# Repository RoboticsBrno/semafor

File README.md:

# Semafor

Traffic light gadget for outdoor games designed for [Helceletka.cz](https://helceletka.cz/).

## Hardware
Board is based on [ESP8266](https://en.wikipedia.org/wiki/ESP8266) microcontroller and large LEDs. It is powered by our power bank and can be managed via WiFi from the user's phone.

## Software
The software is written in [PlatformIO](https://platformio.org/) and is based on the Arduino framework.

<div align="center">
  	<td></td>
	<td></td>
</div>

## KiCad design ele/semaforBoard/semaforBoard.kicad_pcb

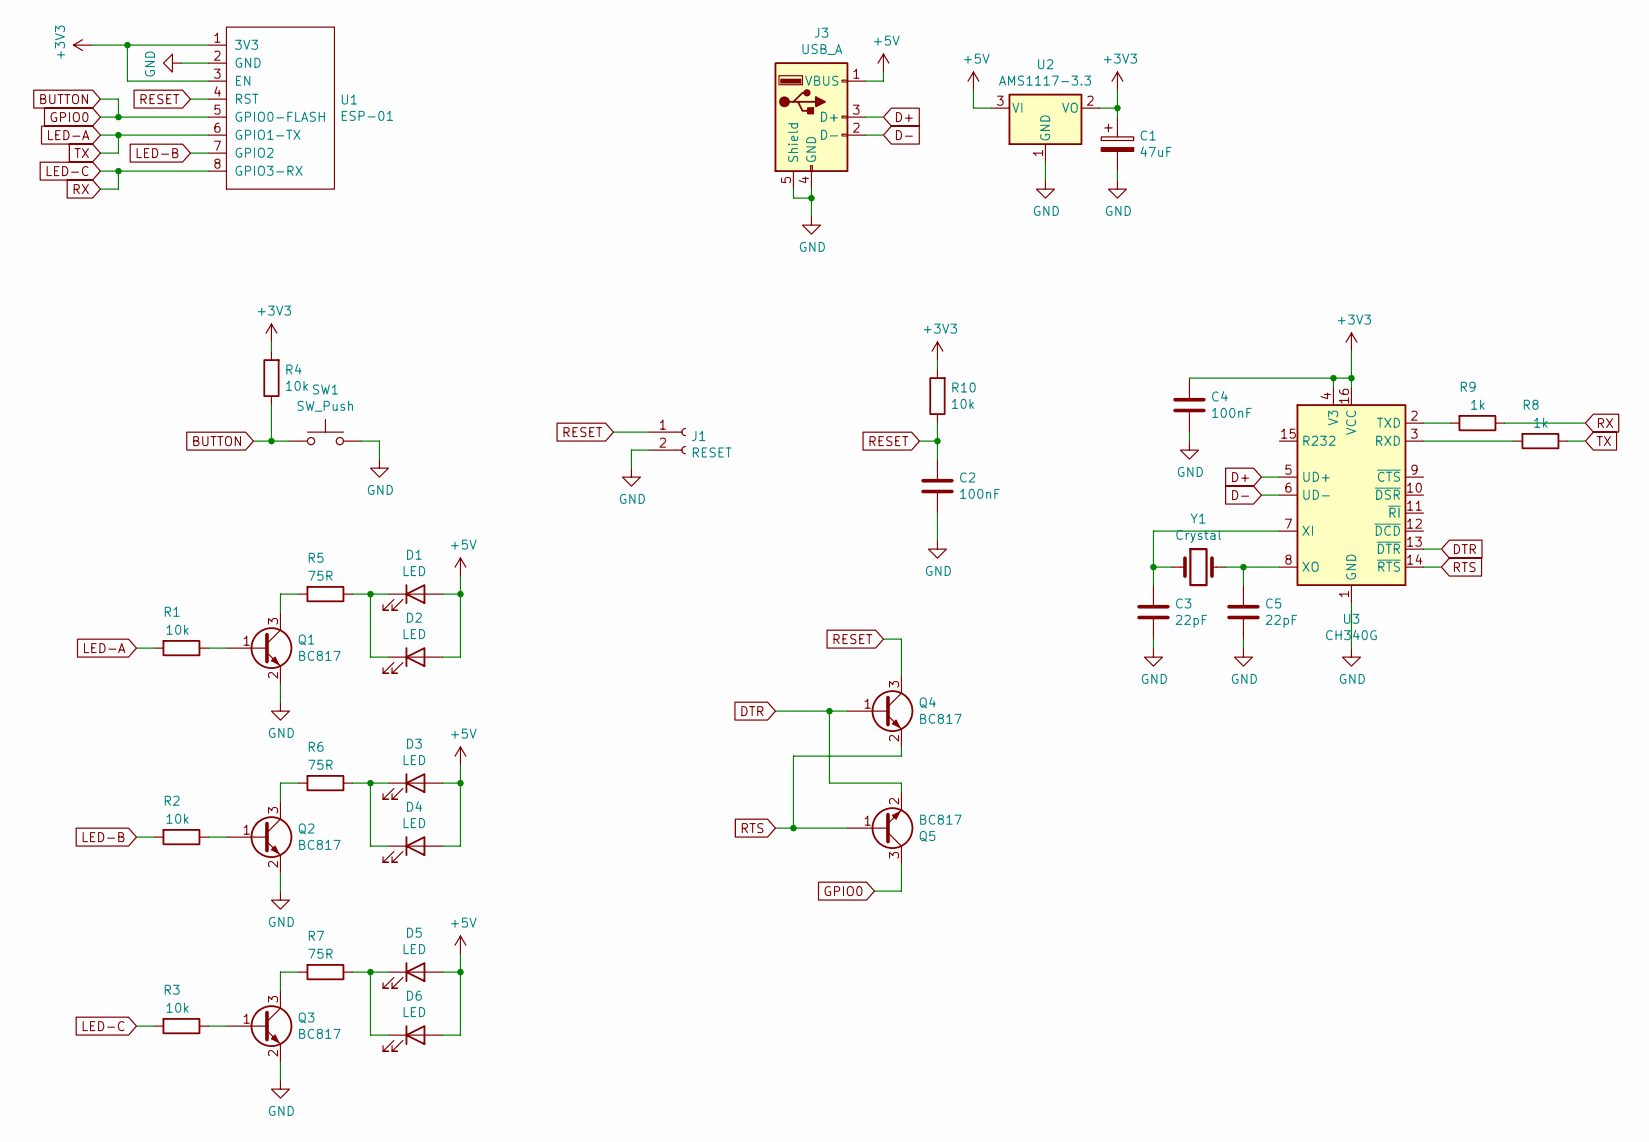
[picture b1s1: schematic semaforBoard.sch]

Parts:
C1: 47uF; CP_Radial_D6.3mm_P2.50mm
C2, C4: 100nF; C_1206_3216Metric_Pad1.42x1.75mm_HandSolder
C3, C5: 22pF; C_1206_3216Metric_Pad1.42x1.75mm_HandSolder
D1, D2, D3, D4, D5, D6: LED; LED_D10.0mm
J1: RESET; PinHeader_1x02_P2.54mm_Vertical
J3: USB_A; USB_A_CNCTech_1001-011-01101_Horizontal
Q1, Q2, Q3, Q4, Q5: BC817; SOT-23
R1, R2, R3, R4, R10: 10k; R_1206_3216Metric_Pad1.42x1.75mm_HandSolder
R5, R6, R7: 75R; R_1206_3216Metric_Pad1.42x1.75mm_HandSolder
R8, R9: 1k; R_1206_3216Metric_Pad1.42x1.75mm_HandSolder
SW1: SW_Push; SW_PUSH_6mm
U1: ESP-01
U2: AMS1117-3.3; SOT-223-3_TabPin2
U3: CH340G; SOIC-16_3.9x9.9mm_P1.27mm
Y1: Crystal; Crystal_HC49-4H_Vertical

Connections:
+3V3: C1.1, C4.1, R4.2, R10.2, U1.1 (3V3), U1.3 (EN), U2.2 (VO), U3.4 (V3), U3.16 (VCC)
+5V: D1.2 (A), D2.2 (A), D3.2 (A), D4.2 (A), D5.2 (A), D6.2 (A), J3.1 (VBUS), U2.3 (VI)
BUTTON: Q5.3 (C), R4.1, SW1.1, U1.5 (GPIO0-FLASH)
D+: J3.3 (D+), U3.5 (UD+)
D-: J3.2 (D-), U3.6 (UD-)
DTR: Q4.1 (B), Q5.2 (E), U3.13 (~DTR)
GND: C1.2, C2.2, C3.2, C4.2, C5.2, J1.2, J3.4 (GND), J3.5 (Shield), Q1.2 (E), Q2.2 (E), Q3.2 (E), SW1.2, U1.2 (GND), U2.1 (GND), U3.1 (GND)
LED-A: R1.2, R8.1, U1.6 (GPIO1-TX)
LED-B: R2.2, U1.7 (GPIO2)
LED-C: R3.2, R9.1, U1.8 (GPIO3-RX)
unnamed: C3.1, U3.7 (XI), Y1.1
unnamed: C5.1, U3.8 (XO), Y1.2
unnamed: D1.1 (K), D2.1 (K), R5.1
unnamed: D3.1 (K), D4.1 (K), R6.1
unnamed: D5.1 (K), D6.1 (K), R7.1
unnamed: Q1.1 (B), R1.1
unnamed: Q1.3 (C), R5.2
unnamed: Q2.1 (B), R2.1
unnamed: Q2.3 (C), R6.2
unnamed: Q3.1 (B), R3.1
unnamed: Q3.3 (C), R7.2
unnamed: R8.2, U3.3 (RXD)
unnamed: R9.2, U3.2 (TXD)
RESET: C2.1, J1.1, Q4.3 (C), R10.1, U1.4 (RST)
RTS: Q4.2 (E), Q5.1 (B), U3.14 (~RTS)

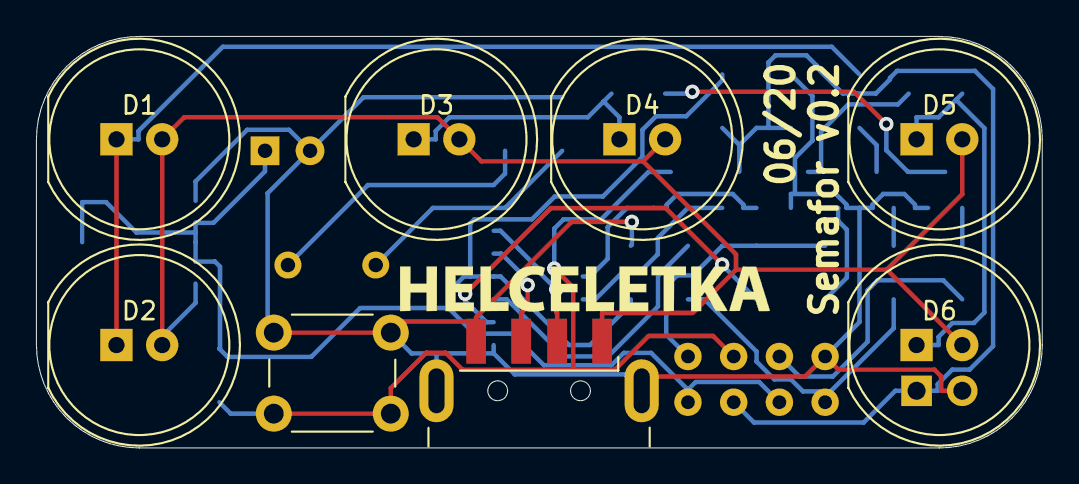
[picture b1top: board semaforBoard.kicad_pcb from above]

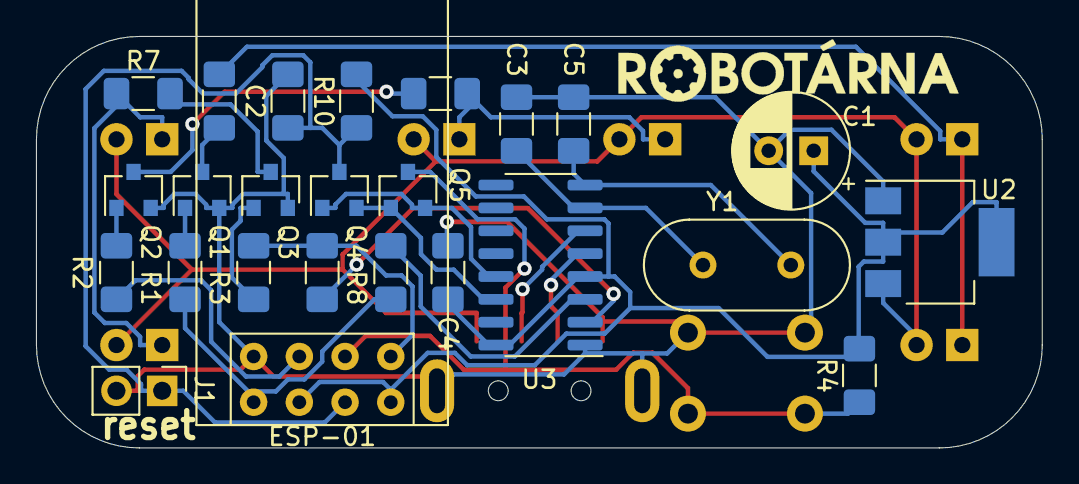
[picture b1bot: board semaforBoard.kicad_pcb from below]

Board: 2 copper layers, 55.9 x 22.9 mm, 35 parts (26 on the bottom side), 25 nets.

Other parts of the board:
G1: LOGO; Robotarna
G2: LOGO; Helceletka

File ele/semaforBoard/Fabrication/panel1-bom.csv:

"Id";"Designator";"Package";"Quantity";"Designation";"Supplier and ref";
1;"REF**,REF**,REF**,REF**,REF**,REF**,REF**,REF**,REF**,REF**,REF**,REF**,REF**,REF**,REF**,REF**,REF**,REF**,REF**,REF**,REF**,REF**,REF**,REF**,REF**,REF**,REF**,REF**,REF**,REF**,REF**,REF**,REF**,REF**,REF**,REF**,REF**,REF**,REF**,REF**,REF**,REF**,REF**,REF**,REF**,REF**,REF**,REF**,REF**,REF**,REF**,REF**,REF**,REF**,REF**,REF**,REF**,REF**,REF**,REF**,REF**,REF**,REF**,REF**,REF**,REF**,REF**,REF**,REF**,REF**,REF**,REF**,REF**,REF**,REF**,REF**,REF**,REF**,REF**,REF**,REF**,REF**,REF**,REF**,REF**,REF**,REF**,REF**,REF**,REF**,REF**,REF**,REF**,REF**,REF**,REF**,REF**,REF**,REF**,REF**,REF**,REF**,REF**,REF**,REF**,REF**,REF**,REF**";"NPTH";108;"NPTH";;;
2;"J1,J1,J1,J1";"PinHeader_1x02_P2.54mm_Vertical";4;"RESET";;;
3;"D6,D5,D4,D3,D2,D1,D6,D5,D4,D3,D2,D1,D6,D5,D4,D3,D2,D1,D6,D5,D4,D3,D2,D1";"LED_D10.0mm";24;"LED";;;
4;"Y1,Y1,Y1,Y1";"Crystal_HC49-4H_Vertical";4;"Crystal";;;
5;"U3,U3,U3,U3";"SOIC-16_3.9x9.9mm_P1.27mm";4;"CH340G";;;
6;"R10,R4,R3,R2,R1,R10,R4,R3,R2,R1,R10,R4,R3,R2,R1,R10,R4,R3,R2,R1";"R_1206_3216Metric_Pad1.42x1.75mm_HandSolder";20;"10k";;;
7;"Q5,Q4,Q3,Q2,Q1,Q5,Q4,Q3,Q2,Q1,Q5,Q4,Q3,Q2,Q1,Q5,Q4,Q3,Q2,Q1";"SOT-23";20;"BC817";;;
8;"C5,C3,C5,C3,C5,C3,C5,C3";"C_1206_3216Metric_Pad1.42x1.75mm_HandSolder";8;"22pF";;;
9;"C4,C2,C4,C2,C4,C2,C4,C2";"C_1206_3216Metric_Pad1.42x1.75mm_HandSolder";8;"100nF";;;
10;"G1,G***,G1,G***,G1,G***,G1,G***";"Robotarna";8;"LOGO";;;
11;"G2,G2,G2,G2";"Helceletka";4;"LOGO";;;
12;"J3,J3,J3,J3";"USB_A_CNCTech_1001-011-01101_Horizontal";4;"USB_A";;;
13;"U1,U1,U1,U1";"ESP-01";4;"ESP-01";;;
14;"U2,U2,U2,U2";"SOT-223-3_TabPin2";4;"AMS1117-3.3";;;
15;"SW1,SW1,SW1,SW1";"SW_PUSH_6mm";4;"SW_Push";;;
16;"R9,R8,R9,R8,R9,R8,R9,R8";"R_1206_3216Metric_Pad1.42x1.75mm_HandSolder";8;"1k";;;
17;"R7,R6,R5,R7,R6,R5,R7,R6,R5,R7,R6,R5";"R_1206_3216Metric_Pad1.42x1.75mm_HandSolder";12;"75R";;;
18;"C1,C1,C1,C1";"CP_Radial_D6.3mm_P2.50mm";4;"47uF";;;

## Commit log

2020-05-22 Test program. First board layout.
2020-05-23 Component placement, logos.
2020-05-26 Removed "tlačítko" marking, mount of button now possible on both-sides. Gen. gerbers.
2020-06-12 Updated schmatic for CH340G.
2020-06-13 10mm leds. PCB routed.
2020-06-14 Panelized using kikit and generated fabrication data.
2020-06-15 Added missing drill file in panel1.zip fabrication file.
2020-06-15 Add Kikit configuratio for automatic panelization
    - add `.travis.yml` and `Makefile` as configuration for automatic panelization with KiKit
2020-06-30 First version of web config page.
2020-06-30 Saving data from website to eeprom.
2020-06-30 Working monopoly.
2020-06-30 Functional "vabicka" and "vlajky" mode.
2020-06-30 Setting SSID using semaforID.
2020-06-30 Functional "tower defence" without flashes.
2020-07-01 Added flashing to tower defence and currentMode web indication.
2020-07-01 Added brightness setting and fixed state transitions.
2020-07-02 Fixed monopoly red initial state.
2020-09-20 Changed R2 LED-B-GPIO2 resistor from 10k to 33k for correct boot in KiCad project and excel production files. Added semafor riddle mode.
2021-06-05 Changed project structure. Most functionality in semafor.cpp.
2021-06-05 Changed SPIFFS to LittleFS
2021-06-05 Moved semaforID from stateVector. Setting it now through url request.
2021-06-05 Updated semaforID init value.
2021-06-06 Removed FS. Now style.css in program code.
2021-06-06 "Hold to Get" mode added UI
2021-06-12 Fix file name, change default IP, improve headers
2021-06-13 Update code
2021-06-22 First Settings transferred
2021-06-23 Fix stateVector filename + try change PIO ini
2021-06-23 Use metronome, serial-led switch, struct edit
2021-06-23 Add start modes (brodcast, receive)
2021-06-24 Brodcast settings start
2021-06-24 Add admin mode
2021-06-30 Add nowe games (minutka , mikrovlnka)
2021-06-30 Deploy RoboticsBrno/semafor to github.com/RoboticsBrno/semafor.git:gh-pages
2022-06-03 FIx minutka game restart - close #4
2023-03-07 Add comments to code
2023-04-05 Add readme
